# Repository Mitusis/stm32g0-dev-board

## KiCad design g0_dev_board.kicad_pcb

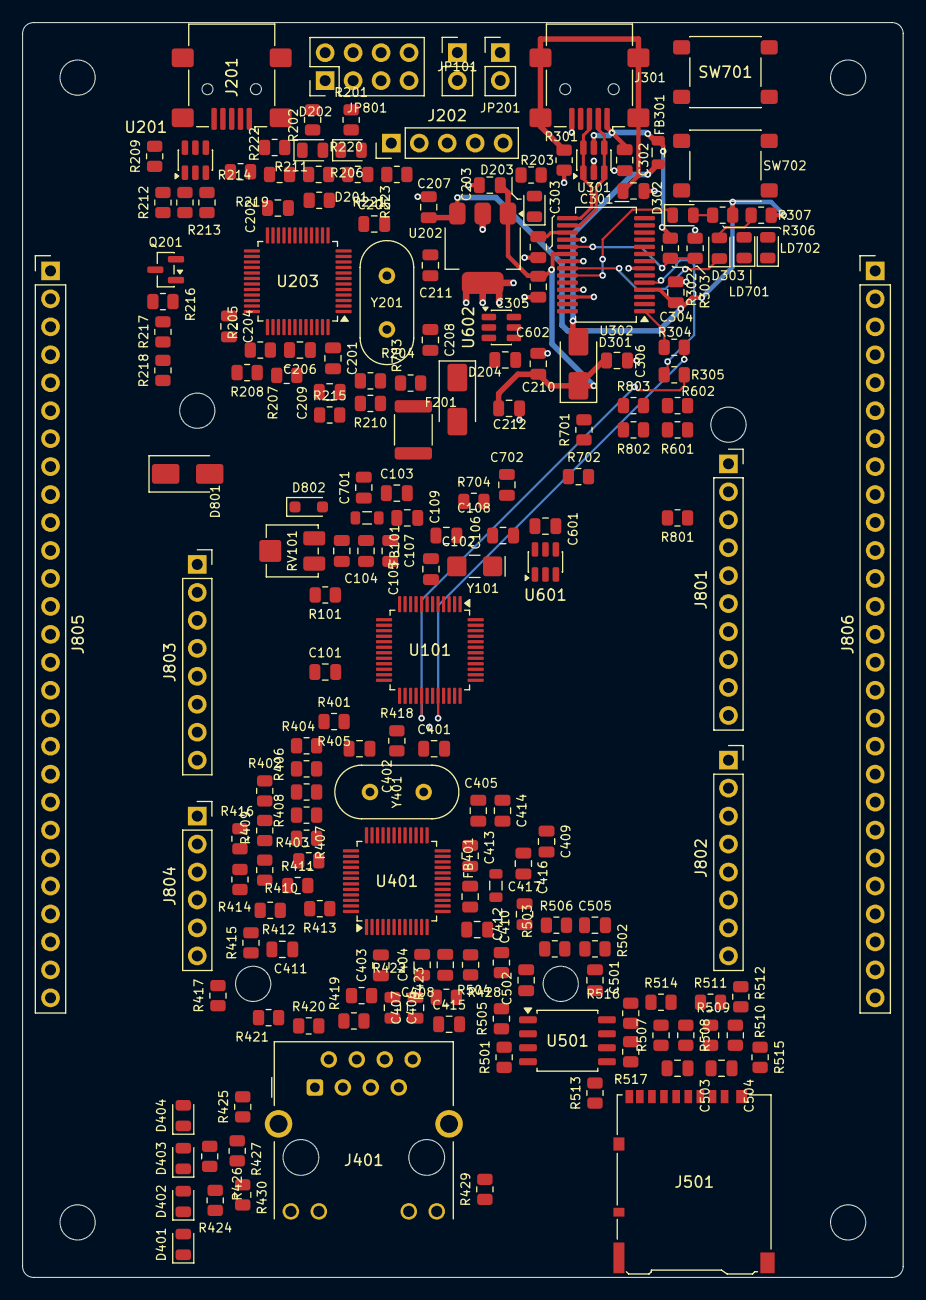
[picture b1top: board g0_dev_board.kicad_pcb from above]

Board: 4 copper layers, 80.0 x 114.0 mm, 198 parts (0 on the bottom side), 152 nets.

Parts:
C101, C102, C103, C105, C107, C201, C202, C204, C205, C209, C212, C303, C304, C305, C403, C404, C405, C408, C410, C412, C413, C503, C505, C701, C702: 100n; C_0805_2012Metric
C104, C203, C206, C306, C416: 4.7u; C_0805_2012Metric
C106, C108: 6.8p C0G; C_0805_2012Metric
C109: 1u; C_0805_2012Metric
C207, C210, C409, C414, C502, C504: 10u; C_0805_2012Metric
C208, C211: 22p; C_0805_2012Metric
C301: 4.7n; C_0805_2012Metric
C302, C415, C417: 10n; C_0805_2012Metric
C401, C402: 33p C0G; C_0805_2012Metric
C406, C407: 6n8; C_0805_2012Metric
C411: 22n; C_0805_2012Metric
C501, C601, C602: 100n X7R; C_0805_2012Metric
D201: LED_Red; LED_0805_2012Metric
D202: LED_Green; LED_0805_2012Metric
D203, D401, D402, D403, D404: LED; LED_0805_2012Metric
D204, D301, D801: B120; D_SMA
D302: TX; LED_0805_2012Metric
D303: RX; LED_0805_2012Metric
D802: BAT54WS; D_SOD-323_HandSoldering
F201: MF-MSMF075-2; Fuse_1812_4532Metric
FB101, FB401: 600R@100MHz 0.5A; L_0805_2012Metric
FB301: 220R@100MHz 2A; L_0805_2012Metric
H1, H2, H3, H4: MountingHole_3.2mm_M3
H801, H802, H803, H804: Arduino_MountingHole_3.2mm
J201, J301: USB_B_Mini; USB_Mini-B_Lumberg_2486_01_Horizontal
J202: F103_SWD; PinHeader_1x05_P2.54mm_Vertical
J401: RJ45_Hanrun_HR911105A_Horizontal
J501: DM3AT-SF-PEJM5; microSD_HC_Hirose_DM3AT-SF-PEJM5
J801: Uno_IOH; PinSocket_1x10_P2.54mm_Vertical
J802: Uno_IOL; PinSocket_1x08_P2.54mm_Vertical
J803: Uno_POWER; PinSocket_1x08_P2.54mm_Vertical
J804: Uno_ANALOG; PinSocket_1x06_P2.54mm_Vertical
J805: J_LA_L; PinHeader_1x27_P2.54mm_Vertical
J806: J_LA_R; PinHeader_1x27_P2.54mm_Vertical
JP101: JP_IDD; PinHeader_1x02_P2.54mm_Vertical
JP201: JP_STL_PWR; PinHeader_1x02_P2.54mm_Vertical
JP801: JP_SWD; PinHeader_2x04_P2.54mm_Vertical
LD701: GREEN; LED_0805_2012Metric
LD702: RED; LED_0805_2012Metric
Q201: MMBT3904; SOT-23
R101, R302, R304, R305: 1k; R_0805_2012Metric
R201, R202, R203, R306, R307, R424, R425, R426, R427, R429, R430, R701: 330; R_0805_2012Metric
R204, R210: 4k7; R_0805_2012Metric
R205, R206, R208, R209, R215, R703, R704: 100k; R_0805_2012Metric
R207, R216, R401, R402, R403, R410, R411, R412, R413, R414, R415, R416, R417, R505, R511, R516, R517: 10k; R_0805_2012Metric
R211, R213, R214, R223, R301, R801, R802, R803: 0; R_0805_2012Metric
R212: 1k5; R_0805_2012Metric
R217: 36k; R_0805_2012Metric
R218, R222: 100; R_0805_2012Metric
R219, R220, R221, R404, R405, R406, R407, R408, R409: 22; R_0805_2012Metric
R303: 2.2k; R_0805_2012Metric
R418: 1M; R_0805_2012Metric
R419, R420, R422, R423: 49R9 1%; R_0805_2012Metric
R421: 10R 1%; R_0805_2012Metric
R428: 12k4 1%; R_0805_2012Metric
R501, R502, R503, R504, R507, R508, R509, R510: 10; R_0805_2012Metric
R506, R512, R513, R514, R515: 47k; R_0805_2012Metric
R601, R602: 4.7k; R_0805_2012Metric
R702: 680; R_0805_2012Metric
RV101: 10k; Potentiometer_Bourns_3314J_Vertical
SW701: RESET; SW_SPST_PTS645Sx43SMTR92
SW702: USER; SW_SPST_PTS645Sx43SMTR92
U101: STM32G0B1CCT6; LQFP-48_7x7mm_P0.5mm
U201, U301: USBLC6-2SC6; SOT-23-6
U202: AP7361C-33E; SOT-223-3_TabPin2
U203: STM32F103CBTx; LQFP-48_7x7mm_P0.5mm
U302: FT232RL; SSOP-28_5.3x10.2mm_P0.65mm
U401: W5500; LQFP-48_7x7mm_P0.5mm
U501: W25Q32JVSSIQ; SOIC-8_5.3x5.3mm_P1.27mm
U601, U602: TMP100; SOT-23-6
Y101: 32.768kHz CL7pF; Crystal_SMD_G8-2Pin_3.2x1.5mm_HandSoldering
Y201: 8MHz; Crystal_HC49-4H_Vertical
Y401: 25MHz; Crystal_HC49-4H_Vertical

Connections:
+3.3V: C207.1, C304.1, C405.1, C414.1, C501.1, C502.1, C503.1, C504.1, C601.1, C602.1, D401.2, D402.2, D403.2, D404.2, FB401.1, J501.4, J803.2, J803.4, J805.2, J806.3, JP101.1, JP201.1, R203.1, R306.2, R307.2, R401.1, R402.1, R403.1, R410.1, R411.1, R412.1, R429.2, R430.2, R505.1, R506.1, R511.1, R512.1, R513.1, R514.1, R515.1, R516.1, R517.1, R601.1, R602.1, R703.1, R704.1, U202.3, U302.4, U401.28, U501.8, U601.3, U601.4, U601.5, U602.4, U602.5
+3V3_MCU: C102.1, C104.1, C105.1, FB101.1, JP101.2, RV101.1, U101.4, U101.6
+3V3_STL: C201.1, C202.1, C204.1, C205.1, C206.1, D201.2, J202.1, JP201.2, Q201.3, R204.1, R215.1, U203.1, U203.9, U203.24, U203.36, U203.48
+5V: C203.1, C210.1, C212.1, C305.1, C306.1, D204.1, D301.1, D801.2, J803.5, J805.4, J806.27, U202.1, U302.20
/A0: J804.1, J805.7, U101.11
/A1: J804.2, J805.8, U101.12
/A2: J804.3, J805.9, U101.17
/A3: J804.4, J805.10, U101.18
/A4: J804.5, J805.11, R802.1, U101.19
/A5: J804.6, J805.12, R803.1, U101.20
/BTN: C702.2, J805.20, R704.2, SW702.2, U101.1
/CARD_DET: C505.1, J501.10, J805.16, R506.2, U101.41
/D0: J802.8, J806.18, U101.14
/D1: J802.7, J806.17, U101.13
/D2: J802.6, J806.16, U101.23
/D3: J802.5, J806.15, U101.22
/D4: J802.4, J806.14, U101.38
/D5: J802.3, J806.13, U101.33
/D6: J802.2, J806.12, U101.45
/D7: J802.1, J806.11, U101.40
/D8: J801.10, J806.10, U101.46
/D9: J801.9, J806.9, U101.28
/D10: J801.8, J806.8, U101.37
/D11: J801.7, J806.7, U101.44
/D12: J801.6, J806.6, U101.43
/D13: J801.5, J806.5, U101.42
/FL_CS: J805.14, R501.1, U101.21
/GPIO_PF0: J805.22, U101.8
/GPIO_PF1: J805.23, U101.9
/I2C1_SCL: J801.1, J806.1, R602.2, R803.2, U101.47, U601.1, U602.1
/I2C1_SDA: J801.2, J806.2, R601.2, R802.2, U101.48, U601.6, U602.6
/LED0: J805.18, R701.1, U101.30
/LED1: J805.19, R702.1, U101.31
/MCU_SWCLK: J805.24, JP801.2, U101.36
/MCU_SWDIO: J805.25, JP801.4, U101.35
/NRST: C103.1, C701.2, D802.2, J805.3, JP801.6, R703.2, SW701.2, U101.10
/POT: C101.1, J805.21, R101.2, U101.15
/SD_CS: J805.15, R507.1, U101.34
/SPI2_MISO: J806.21, R406.1, R504.1, R510.1, U101.26
/SPI2_MOSI: J806.22, R407.1, R503.1, R508.1, U101.27
/SPI2_SCK: J806.20, R405.1, R502.1, R509.1, U101.25
/STL_RESET: JP801.5, R221.2
/STL_SWCLK: JP801.1, R220.2
/STL_SWDIO: JP801.3, R219.2
/U1_RX: J806.26, R304.2, U101.32
/U1_TX: J806.25, R305.2, U101.29
/VREF+: C107.1, C109.1, FB101.2, R801.2, U101.5
/W_CS: J806.23, R404.1, U101.24
/W_INT: J806.24, R408.1, U101.39
/W_RST: J805.17, R409.1, U101.16
/cpu/OSC32_IN: C106.1, U101.2, Y101.1
/cpu/OSC32_OUT: C108.1, U101.3, Y101.2
/ft232rl/FT_3V3: C303.1, U302.17
/ft232rl/FT_D+: J301.3, U301.1, U301.6, U302.15
/ft232rl/FT_D-: J301.2, U301.3, U301.4, U302.16
/ft232rl/FT_RESET_N: R302.2, R303.1, U302.19
/ft232rl/FT_RXLED: D303.1, U302.22
/ft232rl/FT_SHIELD: C301.1, J301.SH, R301.1
/ft232rl/FT_TXLED: D302.1, U302.23
/ft232rl/VBUS_FT: C302.1, FB301.1, J301.1, R302.1, U301.5
/headers/AREF: J801.3, R801.1
/headers/SH_RESET: D802.1, J803.3
/headers/VIN_SH: D801.1, J803.8, J805.6
/st_link/BOOT_0: R205.1, U203.44
/st_link/BOOT_1: R206.1, U203.20
/st_link/F103_NRST: C209.1, J202.4, R215.2, U203.7
/st_link/F103_SWCLK: J202.3, U203.37
/st_link/F103_SWDIO: J202.2, U203.34
/st_link/J201_D+: J201.3, R212.2, R213.1, U201.1, U201.6
/st_link/J201_D-: J201.2, R214.1, U201.3, U201.4
/st_link/LED_STLINK: R201.1, R202.1, U203.30
/st_link/OSC_IN: C208.1, U203.5, Y201.1
/st_link/OSC_OUT: C211.1, U203.6, Y201.2
/st_link/PC13: R207.1, U203.2
/st_link/STL_D+: R213.2, U203.33
/st_link/STL_D-: R214.2, U203.32
/st_link/STL_NRST: R221.1, U203.18
/st_link/STL_PA5: R223.1, U203.15
/st_link/STL_SWCLK: R220.1, R223.2, U203.26
/st_link/STL_SWDIO: R219.1, R222.2, U203.27
/st_link/STL_SWDIO_IN: R222.1, U203.25
/st_link/STL_SWO_IN: R208.1, U203.31
/st_link/T_VCC: R204.2, R210.1, U203.10
/st_link/USB_RENUM: R218.2, U203.38
/st_link/VBUS_STL: F201.1, J201.1, R216.1, U201.5
/w32/SD_CMD: J501.3, R508.2, R512.2
/w32/SD_DAT0: J501.7, R510.2, R513.2
/w32/SD_DAT1: J501.8, R514.2
/w32/SD_DAT2: J501.1, R515.2
/w32/SD_DAT3: J501.2, R507.2, R511.2
/w5500/1V20: C417.1, U401.22
/w5500/3V3A: C403.1, C404.1, C408.1, C409.1, C410.1, C412.1, C413.1, FB401.2, R419.1, R420.1, R421.1, U401.4, U401.8, U401.11, U401.15, U401.17, U401.21
/w5500/ACTLED: J401.10, R426.1, U401.27
/w5500/DUPLED: R425.1, U401.26
/w5500/EXRES1: R428.1, U401.10
/w5500/LINKLED: J401.11, R427.1, U401.25
/w5500/RCT: C415.2, J401.5, R422.2, R423.2
/w5500/RXI_N: C406.1, R422.1, U401.5
/w5500/RXI_P: C407.1, R423.1, U401.6
/w5500/RXN: C406.2, J401.6
/w5500/RXP: C407.2, J401.3
/w5500/SPDLED: R424.1, U401.24
/w5500/TCT: C411.1, J401.4, R421.2
/w5500/TOCAP: C416.1, U401.20
/w5500/TXN: J401.2, R420.2, U401.1
/w5500/TXP: J401.1, R419.2, U401.2
/w5500/W_INTn: R402.2, R408.2, U401.36
/w5500/W_RSTn: R403.2, R409.2, U401.37
/w5500/W_SCSn: R401.2, R404.2, U401.32
/w5500/X0: C402.2, R418.1, U401.31, Y401.1
/w5500/X1: C401.2, R418.2, U401.30, Y401.2
GND: C101.2, C102.2, C103.2, C104.2, C105.2, C106.2, C107.2, C108.2, C109.2, C201.2, C202.2, C203.2, C204.2, C205.2, C206.2, C207.2, C208.2, C209.2, C210.2, C211.2, C212.2, C301.2, C302.2, C303.2, C304.2, C305.2, C306.2, C401.1, C402.1, C403.2, C404.2, C405.2, C408.2, C409.2, C410.2, C411.2, C412.2, C413.2, C414.2, C415.1, C416.2, C417.2, C501.2, C502.2, C503.2, C504.2, C505.2, C601.2, C602.2, C701.1, C702.1, D203.1, J201.5, J201.SH, J202.5, J301.5, J401.8, J401.SH, J501.6, J501.9, J501.SH, J801.4, J803.6, J803.7, J805.1, J805.5, J805.13, J805.26, J805.27, J806.4, J806.19, JP801.7, JP801.8, LD701.1, LD702.1, R205.2, R206.2, R207.2, R208.2, R209.2, R210.2, R211.2, R217.2, R301.2, R303.2, R413.1, R414.1, R415.1, R416.1, R417.1, R428.2, RV101.3, SW701.1, SW702.1, U101.7, U201.2, U202.2, U203.8, U203.23, U203.35, U203.47, U301.2, U302.7, U302.18, U302.21, U302.25, U302.26, U401.3, U401.9, U401.14, U401.16, U401.19, U401.23, U401.29, U401.48, U501.4, U601.2, U602.2, U602.3
unnamed: D201.1, R201.2
unnamed: D202.2, R202.2
unnamed: D202.1, R211.1
unnamed: D203.2, R203.2
unnamed: D204.2, F201.2
unnamed: D301.2, FB301.2
unnamed: D302.2, R306.1
unnamed: D303.2, R307.1
unnamed: D401.1, R424.2
unnamed: D402.1, R425.2
unnamed: D403.1, R426.2
unnamed: D404.1, R427.2
unnamed: J201.4, R209.1
unnamed: J401.9, R430.1
unnamed: J401.12, R429.1
unnamed: J501.5, R509.2
unnamed: LD701.2, R701.2
unnamed: LD702.2, R702.2
unnamed: Q201.1, R216.2, R217.1, R218.1
unnamed: Q201.2, R212.1
unnamed: R101.1, RV101.2
unnamed: R413.2, U401.38
unnamed: R414.2, U401.39
unnamed: R415.2, U401.40
unnamed: R416.2, U401.41
unnamed: R417.2, U401.42
unnamed: R305.1, U302.5
unnamed: R304.1, U302.1
unnamed: R406.2, U401.34
unnamed: R407.2, U401.35
unnamed: R410.2, U401.45
unnamed: R411.2, U401.44
unnamed: R412.2, U401.43
unnamed: R405.2, U401.33
unnamed: R502.2, U501.6
unnamed: R503.2, U501.5
unnamed: R504.2, U501.2
unnamed: R501.2, R505.2, U501.1
unnamed: R517.2, U501.7
unnamed: R516.2, U501.3
